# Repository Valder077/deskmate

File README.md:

# deskmate
A deskmate to keep you company during your late night study sessions(or anytime really!), whenever and wherever. It contains 4 keys that do different things (two interact with the desk pet and two are for start/stopping the pomodoro timer and to reset it). It also has a keychain to suit your studying on the go needs. 

I wanted to make something that would motivate me to study even during times where im just studying alone late at night, to remind me to push through and hence i decided to make deskmate, since I thought it would be really cool and also something that I would find cute and useful. 

## schematic 
This is my schematic 

## PCB
This is how my PCB looks like 

## CAD
This is a picture of my CAD

And this is one more with the components included 

## animations 
You can check out more about animations in my journals 

## Final product 
YAY ITS DONE!

youtube link : https://www.youtube.com/watch?v=puzSfpu7b3g

## BOM
 
 | Part                           | Source                                                                                                                                                                                                                                                       | Cost |
|--------------------------------|--------------------------------------------------------------------------------------------------------------------------------------------------------------------------------------------------------------------------------------------------------------|------|
| XIAO ESP32S3                   | https://shopee.sg/1pc-Seeeduino-Seeed-Studio-XIAO-ESP32-S3-ESP32S3-2.4G-WiFi-Bluetooth-com-BLE-Mesh-5.0-Development-Board-Module-For-Arduino-i.1558808530.40556404696?sp_atk=3c55a6c8-62fd-4a94-ae5c-47d99df13703&xptdk=3c55a6c8-62fd-4a94-ae5c-47d99df13703 | $15  |
| 0.96"" I2C 128x64 OLED Display | Have already                                                                                                                                                                                                                                                 | NA   |
| Cherry MX Switches             | Have already                                                                                                                                                                                                                                                 | NA   |
| Blank keycaps                  | Have already                                                                                                                                                                                                                                                 | NA   |
| PCB                            | JLCPCB                                                                                                                                                                                                                                                       | $18  |
| 3D printed case                | Print myself                                                                                                                                                                                                                                                 | NA   |
|                                |                                                                                                                                                                                                                                                              |      |
|                                | Total                                                                                                                                                                                                                                                        | $33  |

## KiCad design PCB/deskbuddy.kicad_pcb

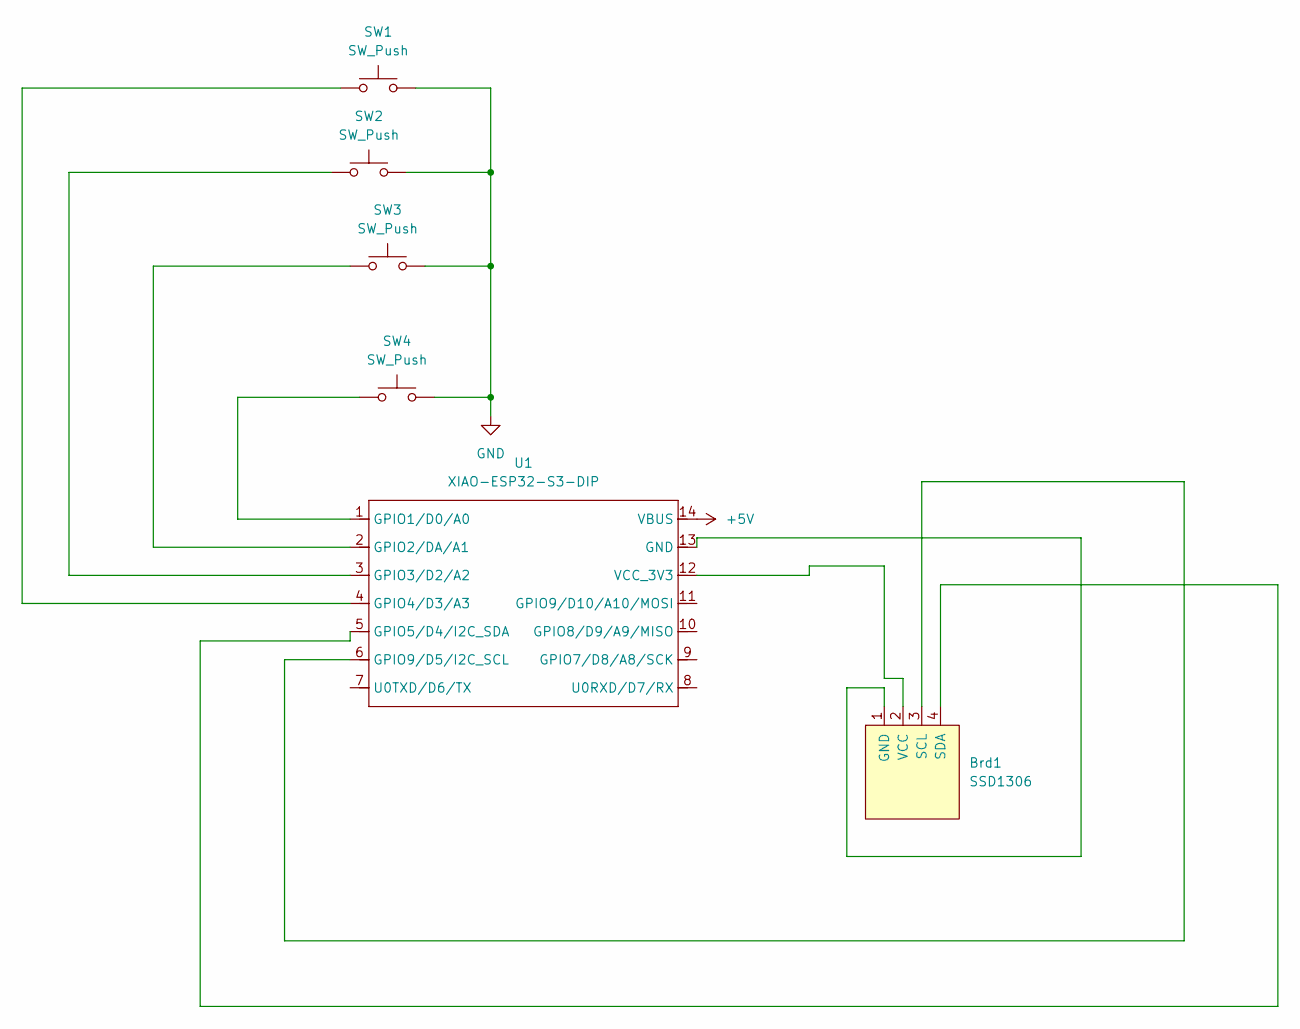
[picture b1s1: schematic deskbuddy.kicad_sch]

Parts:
Brd1: SSD1306; 128x64OLED
SW1, SW2, SW3, SW4: SW_Push; SW_Cherry_MX_1.00u_PCB
U1: XIAO-ESP32-S3-DIP; XIAO-ESP32S3-DIP

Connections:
+5V: U1.14 (VBUS)
GND: SW1.2, SW2.2, SW3.2, SW4.2
unnamed: Brd1.1 (GND), U1.13 (GND)
unnamed: Brd1.3 (SCL), U1.6 (GPIO9/D5/I2C_SCL)
unnamed: Brd1.4 (SDA), U1.5 (GPIO5/D4/I2C_SDA)
unnamed: Brd1.2 (VCC), U1.12 (VCC_3V3)
unnamed: SW4.1, U1.1 (GPIO1/D0/A0)
unnamed: SW3.1, U1.2 (GPIO2/DA/A1)
unnamed: SW2.1, U1.3 (GPIO3/D2/A2)
unnamed: SW1.1, U1.4 (GPIO4/D3/A3)

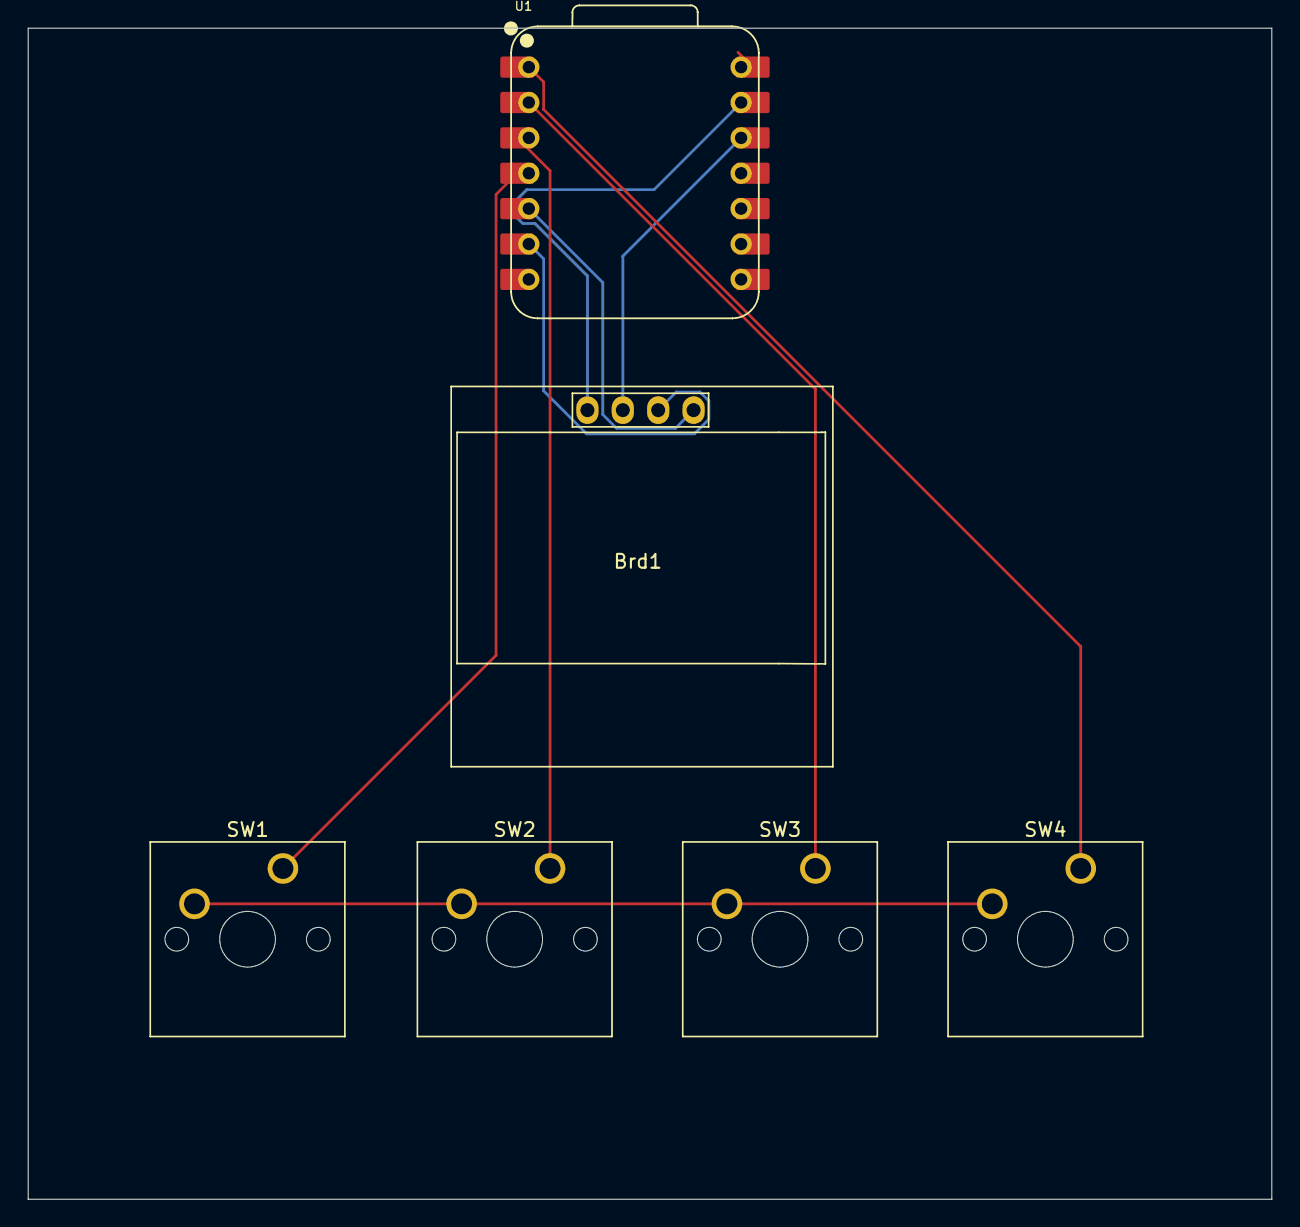
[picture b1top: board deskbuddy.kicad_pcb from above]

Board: 2 copper layers, 89.3 x 84.1 mm, 6 parts (0 on the bottom side), 9 nets.

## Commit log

2025-07-23 Readme edits
2025-07-23 Journal edits
2025-07-23 photos to journal
2025-07-23 more photos
2025-07-23 readme
2025-07-25 journal edits again
2025-07-25 gerbers and pcb
2025-07-25 fullcad update
2025-07-25 firmware
2025-07-25 readme update
2025-07-25 typo
2025-07-25 hours
2025-07-25 images update
2025-07-25 animations
2025-07-25 typo again
2025-07-25 journal changes
2025-07-26 firmware edits
2025-07-26 firmware more updates
2025-08-15 hours edit
2025-08-15 firmware updates
